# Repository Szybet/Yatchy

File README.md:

<h1 align="center">
  Yatchy
</h1>
<p align="center">
  <b>Y</b>our W<b>atchy</b>, fixed and improved, even made modular
</p>

Yatchy is a DIY watch, heavily inspired by the well known [watchy](https://watchy.sqfmi.com/). It focuses on fixing known issues and expanding the potential of it.

#### Key points:
- USBC instead of micro usb
- Better buttons, they won't break easily
- [Better battery life](https://github.com/Szybet/Yatchy/blob/main/hardware/power-consumption/README.md)
- Hardware hackable, easier to self assemble from scratch
- Fixed many issues and improved minor things
- A backlight is possible, *[kind of](https://github.com/Szybet/Yatchy/blob/main/3D/cases/README.md#proof-of-concept-glow-in-the-dark-transparent-filament-with-the-rotated-case)* and many other "extensions"
- [Smaller](https://github.com/Szybet/Yatchy/blob/main/faq.md#dimensions) form factor

<details>
  <summary><h3>Pictures</h3></summary>
The coolest yatchy, contributed by a community member!

<sub>My Yatchy, with a [titanium anodized case, the rotated variant](https://github.com/Szybet/Yatchy/blob/main/3D/cases/JLC3D.md#anodyzed-slm-titanium-tc4-no-polishing)</sub>

<sub>The battery is on the side because it's easier for me to measure power consumption, there are [cases with the battery inside](https://github.com/Szybet/Yatchy/tree/main/3D/cases)</sub>

<sub>A clean soldering job, with some alternative components (compability!)<sub>, yes, I know there is a short on the flex cable, it fell off when cleaning after the picture</sub></sub>

Watchy one the left yatchy on the right, yatchy is smaller (yes, the battery is outside, but it would only increase height, not width/length

<sub>Picture contributed, thanks!</sub>

</details>

## Yatchy features in more detail:

<h4>For regular users</h4>

- Heavy increase in battery life, even with the screen updating every minute <sub>(The esp32c6 has a riscv lp core, which i connected to the screen, which means the device never really wakes up fully to only update the screen, not only that i fixed sqfmi flaws (Using 2 voltage dividers for example) I also use the external crystal clock for the RTC which means no RTC IC... and many more such things)</sub>
- Better buttons, more solid, shouldn't and probably won't break that much if at all. They are also very quiet. If you like the tactile feel of the original buttons, you won't like these ones. Luckly vibration motor feedback is possible.
- Solid USB-C port <sub>(It's THT soldered)</sub>
- no more usb compability problems <sub>(Because the esp32c6 uses native jtag programming)</sub>
- better detection of charging, charge finishing. <sub>(In software it was hacky on the original watchy, there were problems with it, never worked good)</sub>
- support for more wireless protocols, home automation ones, wifi 6 too
- TVS diodes, voltage spike protection - which means no more destroyed devices because watchy doesn't follow any USB spec and allows your device to burn down...
- More precise time, based on some loose math and experiments, it should drift only a minute after a month, compared to the watchy its a lot better, **from experience it's even better than that**

<details>
  <summary><h4>For advanced users</h4></summary>

- Detailed ordering and assembly [guide](https://github.com/Szybet/Yatchy/tree/main/hardware/create-your-own)
- Detailed soldering and testing [guide](https://github.com/Szybet/Yatchy/blob/main/hardware/create-your-own/assembling.md)
- **A module area**, with almost all exposed pins from the esp, power lines, and many gpio pins thanks to the expander IC - You can create your own module, increase the capability of you yatchy without modifying everything inside - solar panel module, encoder instead of the button, sd card module, frontlight module, torchlight module, speaker module, microphone module, some environmental sensors. The only limitation is your imagination (And the size of the module)
   - The default module (In the picture above) allows for for attaching small things without the need for a custom PCB
- All the components are newer, still available and produced. They are also listed, with links to mauser / tme. Ordering a Yatchy PCB and the parts, soldering them themself is possible and easier than the watchy
- All QFN packages IC's on the board have increased pad sizes, so if you are skilled enough to solder QFN packages, here it will be easier
- I used traces teardrops, so more solid traces & pads
- A [hardware test program](https://github.com/Szybet/Yatchy/tree/main/hardware/create-your-own/test-program), which allows testing if all the pads of the esp32c6, which is the hardest part to solder are soldered correctly
- JTAG debugging via usb, yay

</details>

<details>
  <summary><h4>Flaws</h4></summary>

- No battery connector, the module pads are small - so it's not for everyone, harder to use / assembly (solder!) for beginners
- There is no dedicated place for the motor, it needs a dedicated place in the case. Soldering the motor cables also is not easy
- It's watchy like but not watchy case compatible, the size and form factor is the same but the obvious obstacle is USBC, even with it the buttons are different and placed a little off to save some space
- It's a 4 layer PCB, so a bit more costly (With JLCPCB it's still cheap)
- No easy hard reset option, you will need to short pins, but you probably won't need it. <sub>When developing the Yatchy, I only once needed a full reset</sub>
- A complicated license (but still open source!)

</details>

## Software
It's fully supported by [InkWatchy](https://github.com/Szybet/InkWatchy). Maybe a rust firmware in the future? We will see...

## Hardware sources, buying, reselling, license, battery life, time accuracy
Everything explained [here](https://github.com/Szybet/Yatchy/tree/main/hardware)

## Cases, 3D files of the pcb
[Cases here](https://github.com/Szybet/Yatchy/tree/main/3D/cases) and [pcb 3D model here](https://github.com/Szybet/Yatchy/tree/main/3D/pcb)

## [FAQ](https://github.com/Szybet/Yatchy/blob/main/faq.md)

# Community
Create a github issue or get in touch with me on the discord server or matrix space (on top of this read are links)

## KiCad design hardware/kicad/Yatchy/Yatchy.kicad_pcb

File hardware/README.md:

# Other related docs:
1. [Power consumption](https://github.com/Szybet/Yatchy/tree/main/hardware/power-consumption)
2. [Time accuracy](https://github.com/Szybet/Yatchy/blob/main/hardware/time-accuracy.md)
3. [Create your own](https://github.com/Szybet/Yatchy/tree/main/hardware/create-your-own)

## License
<sub>Read all of it :)</sub>

This work is licensed under a [Creative Commons (4.0 International License) Attribution—Noncommercial—Share Alike](https://creativecommons.org/licenses/by-nc-sa/4.0/)

Don't scream "IT'S NOT OPEN SOURCE", let me explain myself.

- First, this work is not a watchy fork, it's a complete redesign obviously inspired by the watchy form factor, but nothing more.
- I don't want SQFMI to steal this design and sell it. Not even if I could profit of it. His bad software, bad communication, sometimes bad and questionable hardware decisions have killed so much potential of the watchy.
- I don't want someone to just make money off it and give nothing back to the project. With that said, calm down, more on that in the commercial section below.
- I don't want for someone to rename it and take the credit for the hard work.

Is it too much to ask for? The whole issue above I have is very known in the open source world, you can see it everywhere around us, here is [Jeff](https://youtu.be/4aaF2HgTVe8?t=84) talking about it. If there appears a open source license which fixes this issue, I will switch to it. 

Oh did I mention **it's is open source anyway?\*\*\*** I share the full source, the schematic, the PCB source files, the needed* (more on it below) software. It's just not the pure open source definition, but the literal interpretation of it. Element of open source like contributing, forking etc. are still allowed and welcome, but with the restrictions above.

<details>
  <summary>Further thoughts about it:</summary>

On https://opensource.org/osd we can see, in the first point "Free Redistribution" and well, first "as a component" hardware can't be a component really, so this point doesn't apply to hardware. The whole point doesn't work for hardware, we know how the world works, it works for software, that's why [InkWatchy](https://github.com/Szybet/InkWatchy) is GPL3. Let's search further, on https://www.oshwa.org/faq/#what-license-to-use we can see the question "Won’t people rip me off?" exactly what I have been searching for! The answer is "Maybe"... ugh... Well their explanation is good but a maybe is too much for me... There is also that: https://mifactori.de/non-commercial-is-not-open-source/

The blog post just shows a general opinion / statement on the internet about this topic, some of the points there make sense to me but some not at all, like `Yes, you do. But so does every patent` Wtf even is this? Sharing something to file a patent is completly different from sharing everything to be reproductible. Also patents can't be compared to hardware things most often because patents say you created something new, but hardware is often a combination of other creations, not entirely new things. Open source is not just "It's commercial, you can ripp me off", it's more than that...

so the entire situation is a joke for me. I can't have a "open source" hardware license without someone "Maybe" ripping me off. So it looks like that:

What I want from "Open source":
- To allow people modify, build their own from scratch, even sell the hardware to some extend, do deep repairs etc. (Which I do, but I'm forced to use the `Creative Commons (4.0 International License) Attribution—Noncommercial—Share Alike` license.)

What I don't want:
- People ripping me off

Sad, it just looks like someone long time ago took a software license, applied it to hardware which doesn't work in the real world and started calling out everyone "Uh oh, it's actually not open source because you are not allowing people to ripp you off"

Rant end, here is what you are left with:

A device that is not open source from the strict definition, but has the bare source for replication available, with elements of open source allowed and the author is open about this all.

* * *

It's not only me having this opinion, other makers also share it:
- https://github.com/o7-machinehum/flipper-blackhat-a33#license

:)

</details>

Update 2026:

Prusa released the [Open community license](https://github.com/OpenCommunityLicence/OpenCommunityLicence) which is basically what I'm saying above but I allow a bit of commerciallity, so that's cool, if they release a plugin like the Micro Business one, but smaller (Nano business?) then I would switch fully to it, so it's less confussion.

## The design of the Yatchy
Yatchy was designed to:
- Be created by yourself. That means it's adjusted to be hand solderable. Sooo that means changed footprints for easier hand soldering. If you can solder SMD without a problem and QFN packets aren't scary for you, but BGA is a bit, then it's for you
- Extremely hackable and modular. The main point is the module and all exposed pads for it
- Optimisation of the ammount of different components, so cheaper
- I tried to use widely available IC's and components. For example, while using some highly mauser only specific IC could improve power consumption a small bit, I preffered the simplicity and availability of the current design

Those design choices have their own flaws:
- It's not possible to order a assembled yatchy from a manufacturer. Not only because of the module, but the modified footprints have not adjusted solder mask (And I don't have the experience and money to test it). **Also to be clear, a stencil is also untested, probably won't work for the reasons explained a sentence ago, you have been warned.** - And with that in mind, let's go to the commercial section

## Commercial
As mentioned above, It's not possible to manufacture yatchy on a mass scale (The original vision ones, doing a "regular" one, sure i gues). I don't even want to, I'm a student, I won't just start a company. I plan to sell a few Yatchy to community members and that's it.

But if you plan to create a Yatchy for yourself (because you have the skills required) you are fully allowed to do so! I will support it fully, you should also consider creating some for people who can't do that. I will fully support it too! Just remember to contribute some docs, code, help, small donation if you create some more and it will be fine :D

So "Commercial use" for the yatchy as in: using it as a cash grab, without giving anything back, which is not allowed.

If you plan to really mass produce them, then we should talk I ques.

**So you want to create your own? There is a doc for that: [Creating your own](https://github.com/Szybet/Yatchy/blob/main/hardware/create-your-own/README.md)**

## The ability to enforce the license
First some explanation:

Yatchy uses esp32c6 which has a lpcore which allows for updating time on the screen in a more efficient way, in a seperate program.

So all this talking is cool but it's just on paper, I can't enforce it, let's be real. That's why I will lock the full source code of the Yatchy lp program until I make back of what I invested. It costed more than I hoped for. Yatchy can still fully function without the lp core, just the battery life will be worse. I will share the source code partially to all yatchy users (also from other potential sellers) to allow to modify it, like the font used. Then I will simply compile it for them. **Yes, it could be converted into a binary library with a header api**, it was simply not done yet as the program is complicated and has a complicated structure. So that scenario is upon a possible request

More details [here](https://github.com/Szybet/Yatchy/blob/main/hardware/lpcore.md)

## The source files
Kicad version 9.0.3 is suggested.

In the kicad folder inside this directory are the design files for the yatchy v1, not yet tested

they (PCB's) are also a bit messy, not fully profesionall, but they do the job, I hope, as I will order them

Yes, the source files reference watchy in a few places, that's because the name "Yatchy" came after, at first this project was planned to be a small watchy fork.

Schematic, iBom can be seen here: https://szybet.github.io/Yatchy/hardware/read-only/index.html

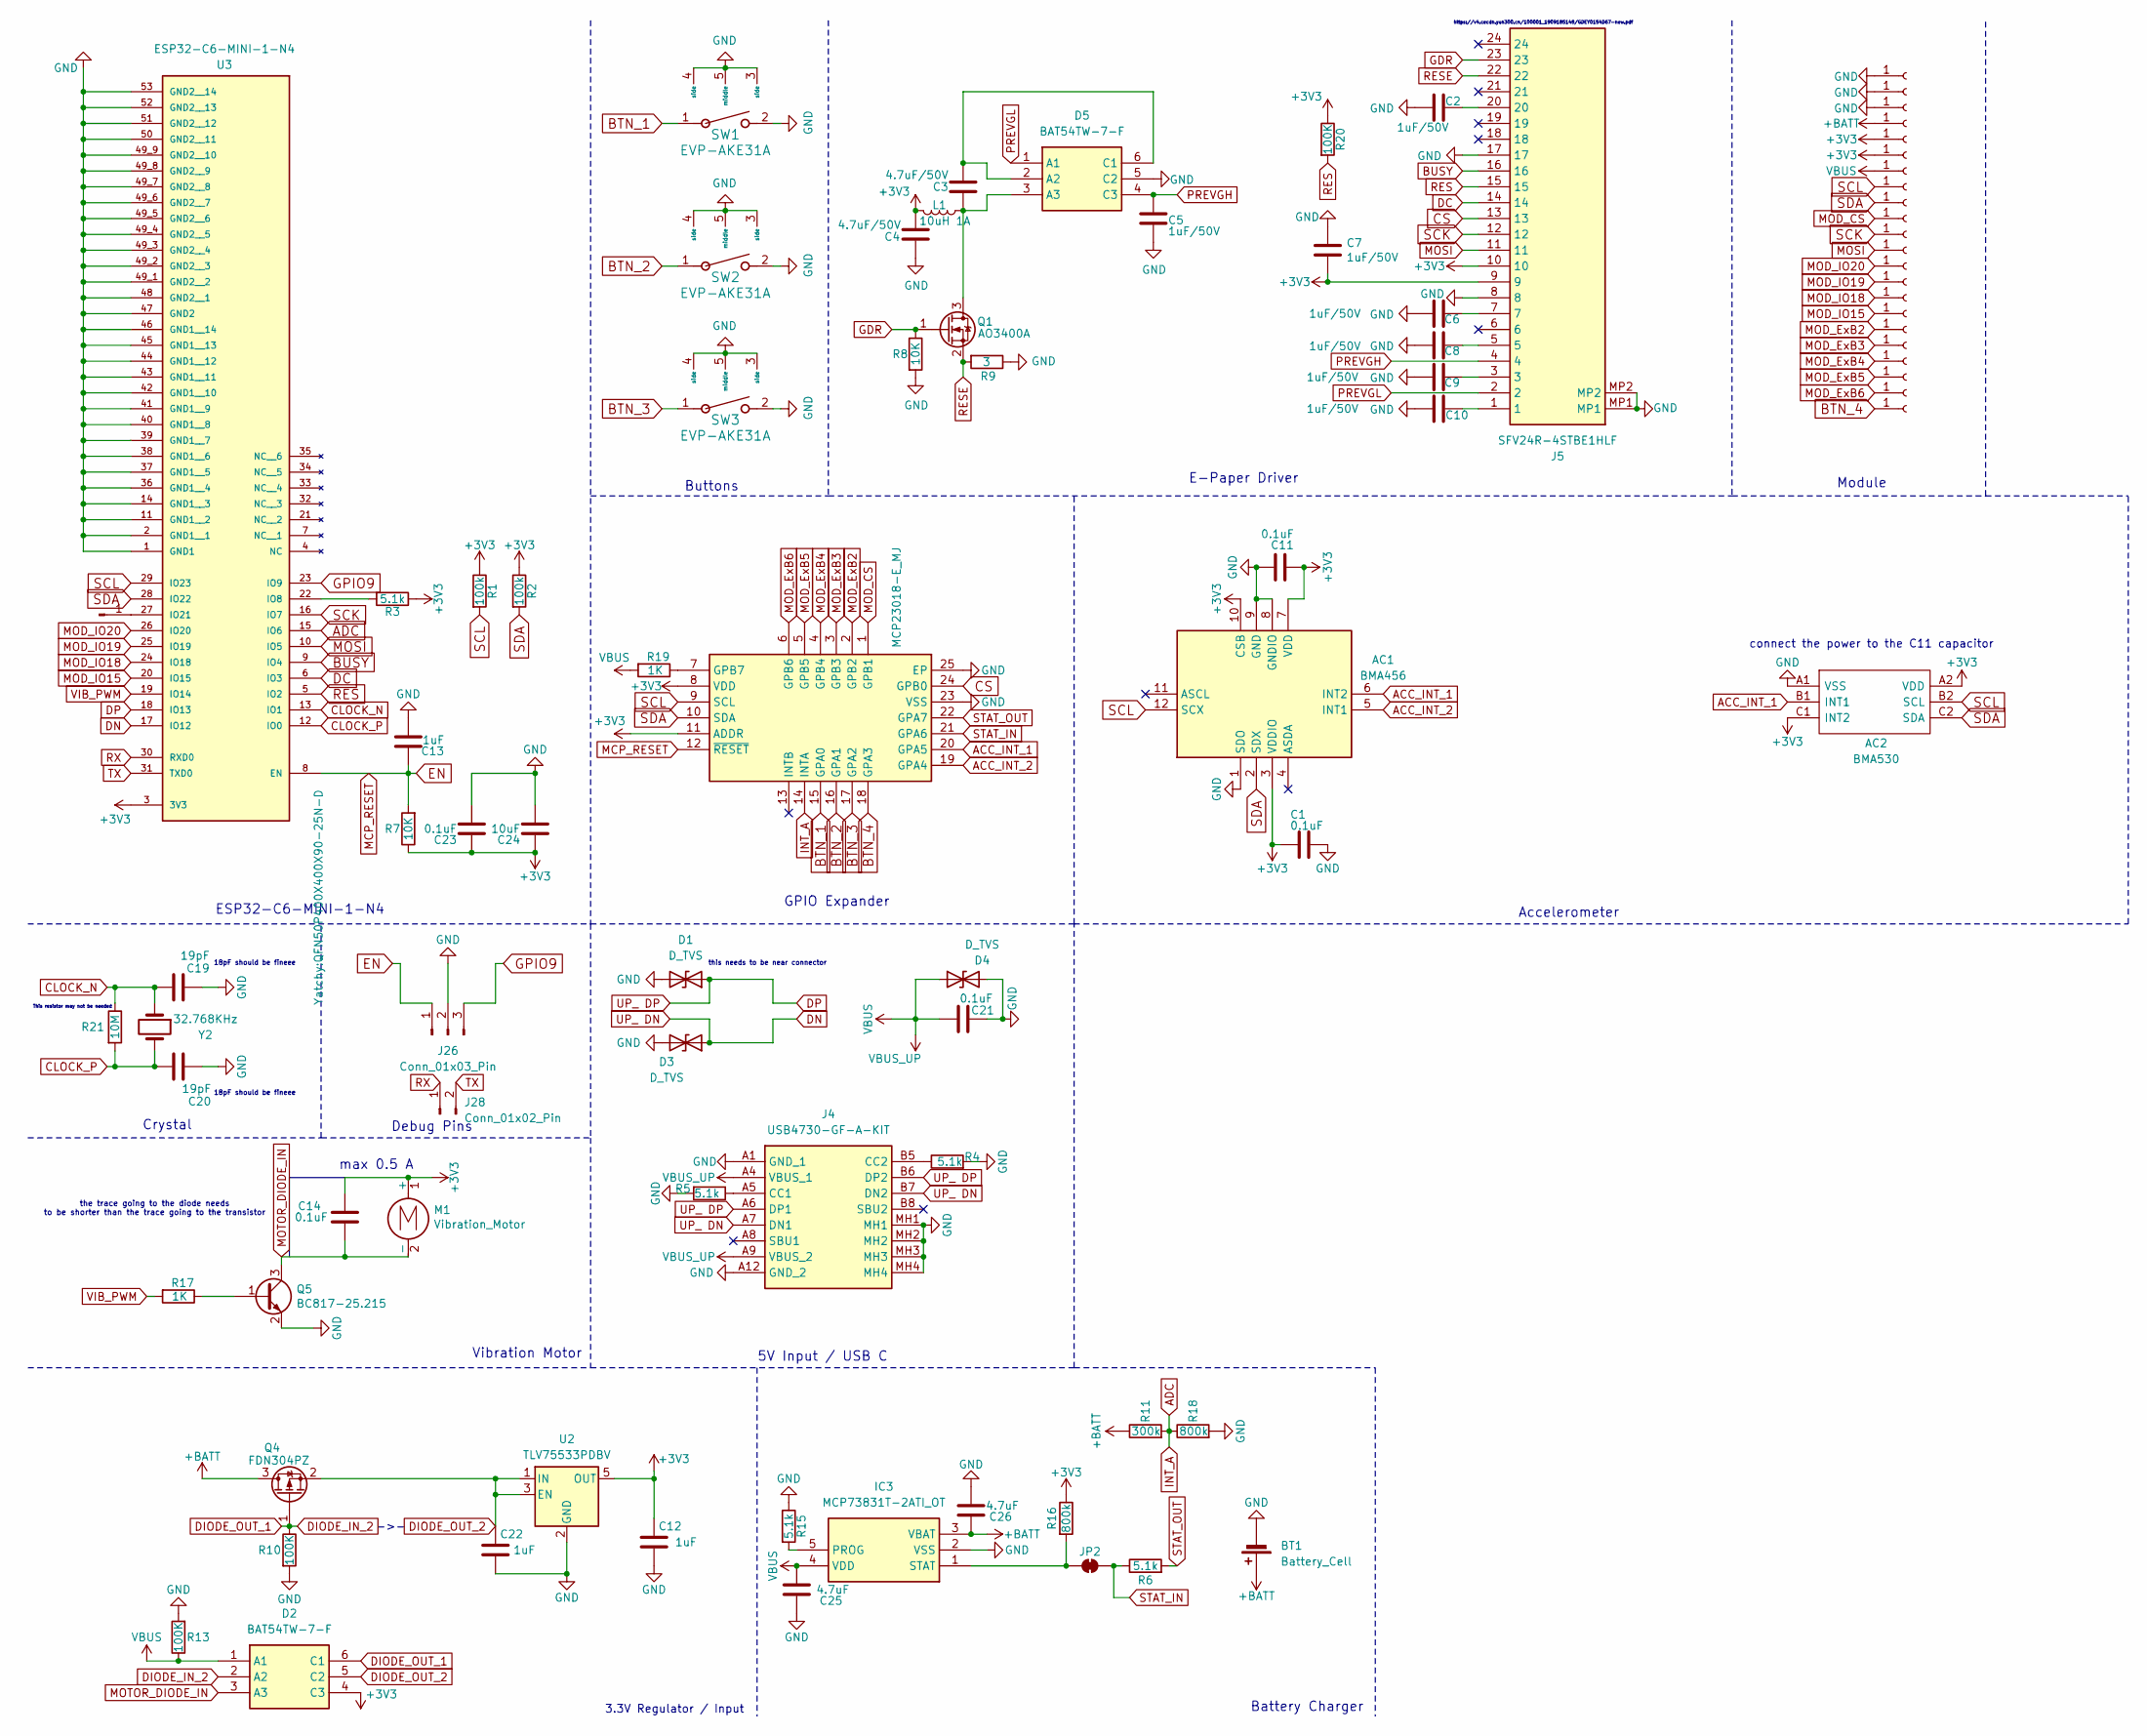
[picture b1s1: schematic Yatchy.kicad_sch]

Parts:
AC1: BMA456; BOSCH_LGA-12; Mouser Part Number 262-BMA456
AC2: BMA530; Mouser Part Number 262-BMA530
BT1: Battery_Cell; Battery_Header
C1, C11, C14, C21, C23: 0.1uF; C_0603_1608Metric
C2, C5, C6, C7, C8, C9, C10: 1uF/50V; C_0603_1608Metric
C3, C4: 4.7uF/50V; C_0805_2012Metric
C12, C13, C22: 1uF; C_0603_1608Metric
C19, C20: 19pF; C_0402_1005Metric
C24: 10uF; C_0603_1608Metric
C25, C26: 4.7uF; C_0805_2012Metric
D1, D3, D4: D_TVS; D_SOD-523
D2, D5: BAT54TW-7-F; SOT65P222X110-6N; Manufacturer_Part_Number BAT54TW-7-F
IC2: MCP23018-E_MJ; QFN50P400X400X90-25N-D; Manufacturer_Part_Number MCP23018-E/MJ
IC3: MCP73831T-2ATI_OT; SOT95P270X145-5N; Manufacturer_Part_Number MCP73831T-2ATI/OT
J1, J2, J3, J6, J7, J8, J9, J10, J11, J12, J13, J14, J15, J16, J19, J20, J21, J22, J23, J24, J25, J27: MOD_CONN; mod_Connector
J4: USB4730-GF-A-KIT; USB4730GFAKIT; Mouser Part Number 640-USB4730GFAKIT
J5: SFV24R-4STBE1HLF; SFV24R4STBE1HLF; Manufacturer_Part_Number SFV24R-4STBE1HLF
J17: Conn_01x01_Pin; testpoint
J26: Conn_01x03_Pin; PinHeader_1x03_P2.00mm_Horizontal_Small
J28: Conn_01x02_Pin; PinHeader_1x02_P2.00mm_Vertical
JP2: SolderJumper_2_Bridged; SolderJumper_Bridged_Small
L1: 10uH 1A; HPI0530-100
M1: Vibration_Motor; Motor_Header
Q1: AO3400A; SOT-23
Q4: FDN304PZ; SOT-23
Q5: BC817-25.215; SOT-23
R1, R2: 100k; R_0402_1005Metric
R3, R4, R5, R6, R15: 5.1k; R_0402_1005Metric
R7, R8: 10K; R_0402_1005Metric
R9: 3; R_0402_1005Metric
R10, R13, R20: 100K; R_0402_1005Metric
R11: 300k; R_0402_1005Metric
R16, R18: 800k; R_0402_1005Metric
R17, R19: 1K; R_0402_1005Metric
R21: 10M; R_0402_1005Metric
SW1, SW2, SW3: EVP-AKE31A; SW_EVP-AKE31A_PAN
U2: TLV75533PDBV; SOT-23-5
U3: ESP32-C6-MINI-1-N4; XCVR_ESP32-C6-MINI-1-N4; PARTREV 1.0
Y2: 32.768KHz; XTAL_9HT10_TXC

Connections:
+3V3: AC1.3 (VDDIO), AC1.7 (VDD), AC1.10 (CSB), AC2.A2 (VDD), AC2.C1 (INT2), C1.2, C4.1, C7.2, C11.2, C12.1, C14.1, C23.1, C24.1, D2.4 (C3), IC2.8 (VDD), IC2.11 (ADDR), J5.9, J5.10, J6.1, J25.1, L1.2, M1.1 (+), R1.1, R2.1, R3.1, R7.1, R16.1, R20.1, U2.5 (OUT), U3.3 (3V3)
+BATT: BT1.1 (+), C26.2, IC3.3 (VBAT), J3.1, Q4.3 (D), R11.1
ACC_INT_1: AC1.6 (INT2), AC2.B1 (INT1), IC2.20 (GPA5)
ACC_INT_2: AC1.5 (INT1), IC2.19 (GPA4)
ADC: IC2.14 (INTA), R11.2, R18.1, U3.15 (IO6)
BTN_1: IC2.15 (GPA0), SW1.1
BTN_2: IC2.16 (GPA1), SW2.1
BTN_3: IC2.17 (GPA2), SW3.1
BTN_4: IC2.18 (GPA3), J24.1
BUSY: J5.16, U3.9 (IO4)
CLOCK_N: C19.1, R21.1, U3.13 (IO1), Y2.1
CLOCK_P: C20.1, R21.2, U3.12 (IO0), Y2.2
CS: IC2.24 (GPB0), J5.13
DC: J5.14, U3.6 (IO3)
DIODE_IN_2: D2.2 (A2), D2.6 (C1), Q4.1 (G), R10.1
DIODE_OUT_2: C22.1, D2.5 (C2), Q4.2 (S), U2.1 (IN), U2.3 (EN)
DN: D3.1 (A1), J4.A7 (DN1), J4.B7 (DN2), U3.17 (IO12)
DP: D1.1 (A1), J4.A6 (DP1), J4.B6 (DP2), U3.18 (IO13)
EN: C13.1, IC2.12 (~RESET), J26.1, R7.2, U3.8 (EN)
GDR: J5.23, Q1.1 (G), R8.1
GND: AC1.1 (SDO), AC1.8 (GNDIO), AC1.9 (GND), AC2.A1 (VSS), BT1.2 (-), C1.1, C2.2, C4.2, C5.2, C6.2, C7.1, C8.2, C9.2, C10.2, C11.1, C12.2, C13.2, C19.2, C20.2, C21.2, C22.2, C23.2, C24.2, C25.2, C26.1, D1.2 (A2), D3.2 (A2), D4.2 (A2), D5.5 (C2), IC2.23 (VSS), IC2.25 (EP), IC3.2 (VSS), J1.1, J2.1, J4.A1 (GND_1), J4.A12 (GND_2), J4.MH1, J4.MH2, J4.MH3, J4.MH4, J5.8, J5.17, J5.MP1, J5.MP2, J26.2, J27.1, Q5.2 (E), R4.2, R5.2, R8.2, R9.1, R10.2, R13.2, R15.1, R18.2, SW1.2, SW1.3 (side), SW1.4 (side), SW1.5 (middle), SW2.2, SW2.3 (side), SW2.4 (side), SW2.5 (middle), SW3.2, SW3.3 (side), SW3.4 (side), SW3.5 (middle), U2.2 (GND), U3.1 (GND1), U3.2 (GND1__1), U3.11 (GND1__2), U3.14 (GND1__3), U3.36 (GND1__4), U3.37 (GND1__5), U3.38 (GND1__6), U3.39 (GND1__7), U3.40 (GND1__8), U3.41 (GND1__9), U3.42 (GND1__10), U3.43 (GND1__11), U3.44 (GND1__12), U3.45 (GND1__13), U3.46 (GND1__14), U3.47 (GND2), U3.48 (GND2__1), U3.49_1 (GND2__2), U3.49_2 (GND2__3), U3.49_3 (GND2__4), U3.49_4 (GND2__5), U3.49_5 (GND2__6), U3.49_6 (GND2__7), U3.49_7 (GND2__8), U3.49_8 (GND2__9), U3.49_9 (GND2__10), U3.50 (GND2__11), U3.51 (GND2__12), U3.52 (GND2__13), U3.53 (GND2__14)
GPIO9: J26.3, U3.23 (IO9)
MOD_CS: IC2.1 (GPB1), J10.1
MOD_ExB2: IC2.2 (GPB2), J19.1
MOD_ExB3: IC2.3 (GPB3), J20.1
MOD_ExB4: IC2.4 (GPB4), J21.1
MOD_ExB5: IC2.5 (GPB5), J22.1
MOD_ExB6: IC2.6 (GPB6), J23.1
MOD_IO15: J16.1, U3.20 (IO15)
MOD_IO18: J15.1, U3.24 (IO18)
MOD_IO19: J14.1, U3.25 (IO19)
MOD_IO20: J13.1, U3.26 (IO20)
MOSI: J5.11, J12.1, U3.10 (IO5)
MOTOR_DIODE_IN: C14.2, D2.3 (A3), M1.2 (-), Q5.3 (C)
unnamed: C2.1, J5.20
unnamed: C6.1, J5.7
unnamed: C8.1, J5.5
unnamed: C9.1, J5.3
unnamed: C10.1, J5.1
unnamed: C3.1, D5.2 (A2), D5.6 (C1)
unnamed: C3.2, D5.3 (A3), L1.1, Q1.3 (D)
unnamed: IC2.7 (GPB7), R19.1
unnamed: IC3.5 (PROG), R15.2
unnamed: IC3.1 (STAT), JP2.1 (A), R16.2
unnamed: J4.A5 (CC1), R5.1
unnamed: J4.B5 (CC2), R4.1
unnamed: J17.1, U3.27 (IO21)
unnamed: Q5.1 (B), R17.1
unnamed: R3.2, U3.22 (IO8)
PREVGH: C5.1, D5.4 (C3), J5.4
PREVGL: D5.1 (A1), J5.2
RES: J5.15, R20.2, U3.5 (IO2)
RESE: J5.22, Q1.2 (S), R9.2
RX: J28.1, U3.30 (RXD0)
SCK: J5.12, J11.1, U3.16 (IO7)
SCL: AC1.12 (SCX), AC2.B2 (SCL), IC2.9 (SCL), J8.1, R1.2, U3.29 (IO23)
SDA: AC1.2 (SDX), AC2.C2 (SDA), IC2.10 (SDA), J9.1, R2.2, U3.28 (IO22)
STAT_IN: IC2.21 (GPA6), JP2.2 (B), R6.1
STAT_OUT: IC2.22 (GPA7), R6.2
TX: J28.2, U3.31 (TXD0)
VBUS: C21.1, C25.1, D2.1 (A1), D4.1 (A1), IC3.4 (VDD), J4.A4 (VBUS_1), J4.A9 (VBUS_2), J7.1, R13.1, R19.2
VIB_PWM: R17.2, U3.19 (IO14)

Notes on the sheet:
This resistor may not be needed
->-
ESP32-C6-MINI-1-N4
the trace going to the diode needs to be shorter than the trace going to the transistor
18pF should be fineee
5V Input / USB C
Battery Charger
Buttons
connect the power to the C11 capacitor
Vibration Motor
max 0.5 A
GPIO Expander
Crystal
Module
3.3V Regulator / Input
https://v4.cecdn.yun300.cn/100001_1909185148/GDEY0154D67-new.pdf
Debug Pins
this needs to be near connector
Accelerometer
E-Paper Driver

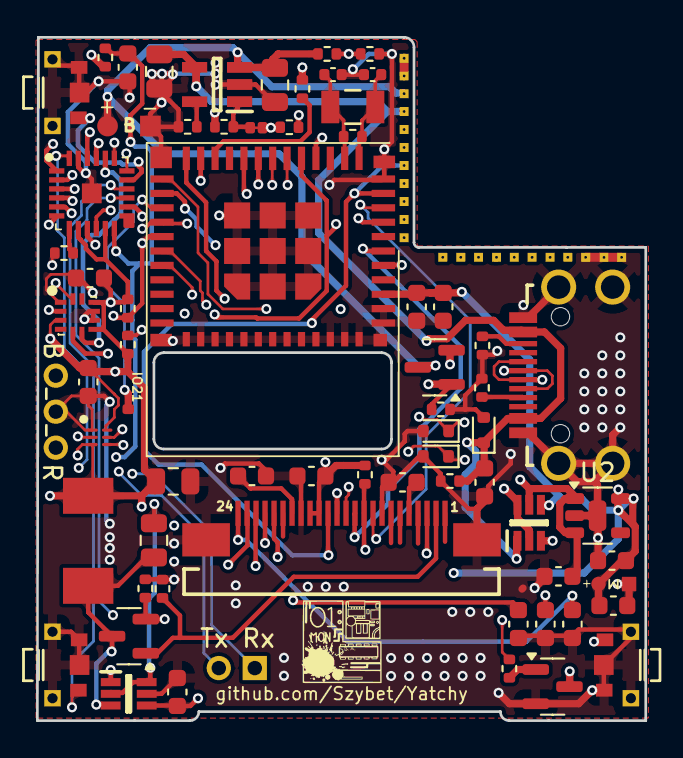
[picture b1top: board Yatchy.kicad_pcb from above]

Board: 4 copper layers, 33.8 x 38.0 mm, 90 parts (0 on the bottom side), 62 nets.

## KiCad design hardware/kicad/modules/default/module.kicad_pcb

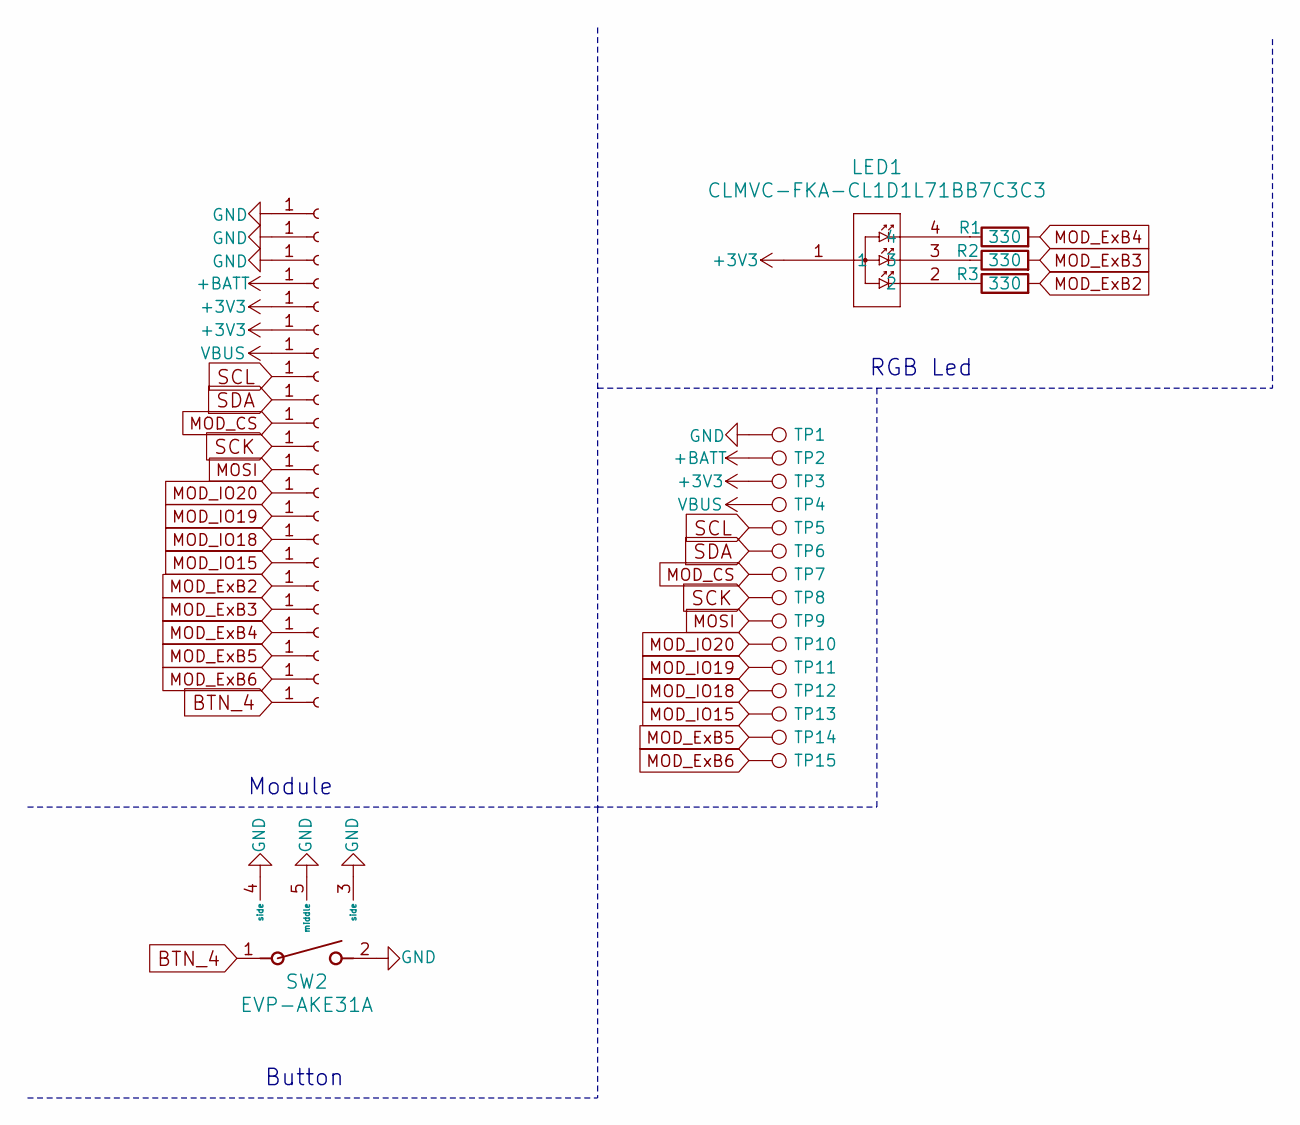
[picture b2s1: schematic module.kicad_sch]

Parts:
J1, J2, J3, J4, J5, J6, J7, J8, J9, J10, J11, J12, J13, J14, J15, J16, J17, J18, J19, J20, J21, J22: MOD_CONN; mod_Connector
LED1: CLMVC-FKA-CL1D1L71BB7C3C3; CLMVC-FKA-CL1D1L71BB7C3C3_CRE
R1, R2, R3: 330; R_0402_1005Metric
SW2: EVP-AKE31A; SW_EVP-AKE31A_PAN
TP1, TP2, TP3, TP4, TP5, TP6, TP7, TP8, TP9, TP10, TP11, TP12, TP13, TP14, TP15: TestPoint; TestPoint_THTPad_D1.0mm_Drill0.5mm

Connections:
+3V3: J5.1, J6.1, LED1.1, TP3.1; also elsewhere on the board
+BATT: J4.1, TP2.1
BTN_4: J22.1, SW2.1
GND: J1.1, J2.1, J3.1, SW2.2, SW2.3 (side), SW2.4 (side), SW2.5 (middle), TP1.1
MOD_CS: J10.1, TP7.1
MOD_ExB2: J17.1, R3.2; also elsewhere on the board
MOD_ExB3: J18.1, R2.2; also elsewhere on the board
MOD_ExB4: J19.1, R1.2; also elsewhere on the board
MOD_ExB5: J20.1, TP14.1; also elsewhere on the board
MOD_ExB6: J21.1, TP15.1
MOD_IO15: J16.1, TP13.1
MOD_IO18: J15.1, TP12.1
MOD_IO19: J14.1, TP11.1
MOD_IO20: J13.1, TP10.1
MOSI: J12.1, TP9.1
unnamed 16: LED1.2, R3.1; also elsewhere on the board
unnamed 17: LED1.3, R2.1; also elsewhere on the board
unnamed 18: LED1.4, R1.1; also elsewhere on the board
SCK: J11.1, TP8.1
SCL: J8.1, TP5.1
SDA: J9.1, TP6.1
VBUS: J7.1, TP4.1

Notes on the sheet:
RGB Led
Button
Module

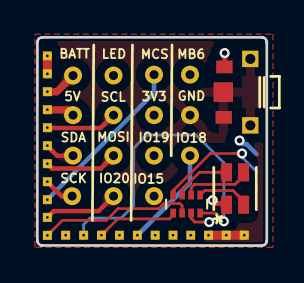
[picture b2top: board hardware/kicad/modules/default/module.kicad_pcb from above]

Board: 4 copper layers, 12.7 x 11.6 mm, 41 parts (1 on the bottom side), 23 nets.

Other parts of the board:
D1: LED; LED_0402_1005Metric
RN1: 330 ohm; R_Array_Concave_4x0402

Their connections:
+3V3: D1.2 (A); also elsewhere on the board
MOD_ExB2: RN1.2 (R2.1); also elsewhere on the board
MOD_ExB3: RN1.3 (R3.1); also elsewhere on the board
MOD_ExB4: RN1.4 (R4.1); also elsewhere on the board
MOD_ExB5: RN1.1 (R1.1); also elsewhere on the board
unnamed: D1.1 (K), RN1.8 (R1.2)
unnamed 16: RN1.7 (R2.2); also elsewhere on the board
unnamed 17: RN1.6 (R3.2); also elsewhere on the board
unnamed 18: RN1.5 (R4.2); also elsewhere on the board

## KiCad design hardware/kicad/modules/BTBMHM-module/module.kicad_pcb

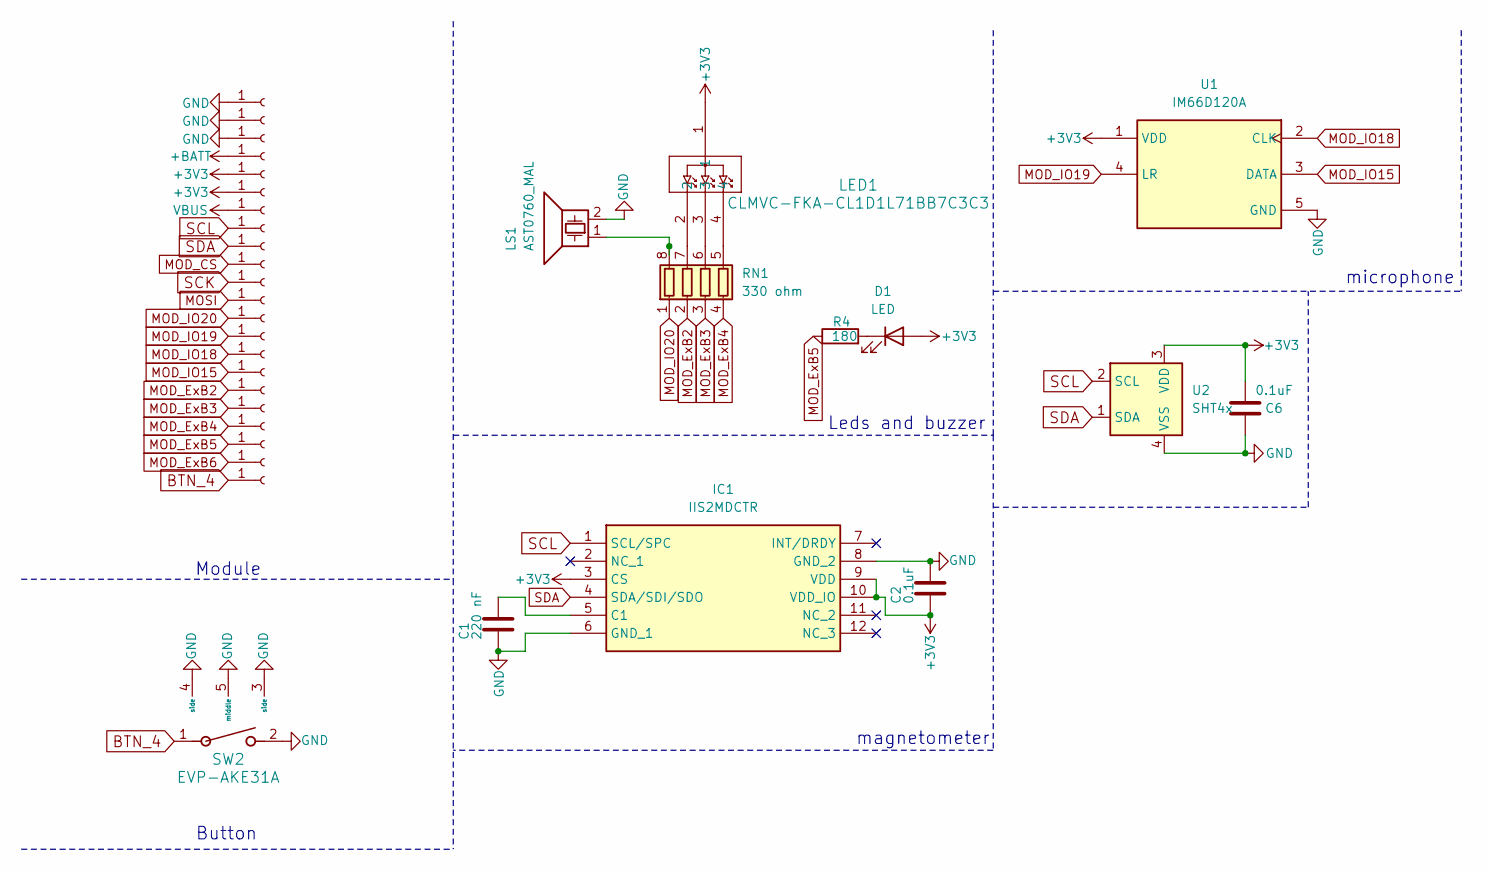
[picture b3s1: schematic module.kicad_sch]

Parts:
C1: 220 nF; C_0603_1608Metric
C2, C6: 0.1uF; C_0603_1608Metric
D1: LED; LED_0402_1005Metric
IC1: IIS2MDCTR; BOSCH_LGA-12; Mouser Part Number 511-IIS2MDCTR
J1, J2, J3, J4, J5, J6, J7, J8, J9, J10, J11, J12, J13, J14, J15, J16, J17, J18, J19, J20, J21, J22: MOD_CONN; mod_Connector
LED1: CLMVC-FKA-CL1D1L71BB7C3C3; CLMVC-FKA-CL1D1L71BB7C3C3_CRE
LS1: AST0760_MAL
R4: 180; R_0402_1005Metric
RN1: 330 ohm; R_Array_Concave_4x0402
SW2: EVP-AKE31A; SW_EVP-AKE31A_PAN
U1: IM66D120A; IFX-PG-TLGA-5-6-V
U2: SHT4x; Sensirion_DFN-4_1.5x1.5mm_P0.8mm_SHT4x_NoCentralPad

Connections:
+3V3: C2.2, C6.2, D1.2 (A), IC1.3 (CS), IC1.9 (VDD), IC1.10 (VDD_IO), J5.1, J6.1, LED1.1, U1.1 (VDD), U2.3 (VDD)
+BATT: J4.1
BTN_4: J22.1, SW2.1
GND: C1.2, C2.1, C6.1, IC1.6 (GND_1), IC1.8 (GND_2), J1.1, J2.1, J3.1, LS1.2, SW2.2, SW2.3 (side), SW2.4 (side), SW2.5 (middle), U1.5 (GND), U2.4 (VSS)
MOD_CS: J10.1
MOD_ExB2: J17.1, RN1.2 (R2.1)
MOD_ExB3: J18.1, RN1.3 (R3.1)
MOD_ExB4: J19.1, RN1.4 (R4.1)
MOD_ExB5: J20.1, R4.1
MOD_ExB6: J21.1
MOD_IO15: J16.1, U1.3 (DATA)
MOD_IO18: J15.1, U1.2 (CLK)
MOD_IO19: J14.1, U1.4 (LR)
MOD_IO20: J13.1, RN1.1 (R1.1)
MOSI: J12.1
unnamed: D1.1 (K), R4.2
unnamed: C1.1, IC1.5 (C1)
unnamed: LS1.1, RN1.8 (R1.2)
unnamed: LED1.2, RN1.7 (R2.2)
unnamed: LED1.3, RN1.6 (R3.2)
unnamed: LED1.4, RN1.5 (R4.2)
SCK: J11.1
SCL: IC1.1 (SCL/SPC), J8.1, U2.2 (SCL)
SDA: IC1.4 (SDA/SDI/SDO), J9.1, U2.1 (SDA)
VBUS: J7.1

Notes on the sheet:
magnetometer
microphone
Button
Leds and buzzer
Module

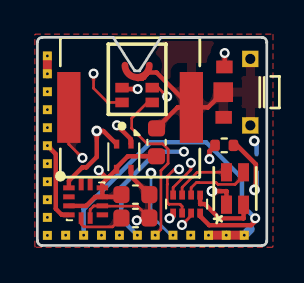
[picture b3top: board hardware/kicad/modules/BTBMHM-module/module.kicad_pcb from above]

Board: 4 copper layers, 12.7 x 11.6 mm, 34 parts (1 on the bottom side), 19 nets.

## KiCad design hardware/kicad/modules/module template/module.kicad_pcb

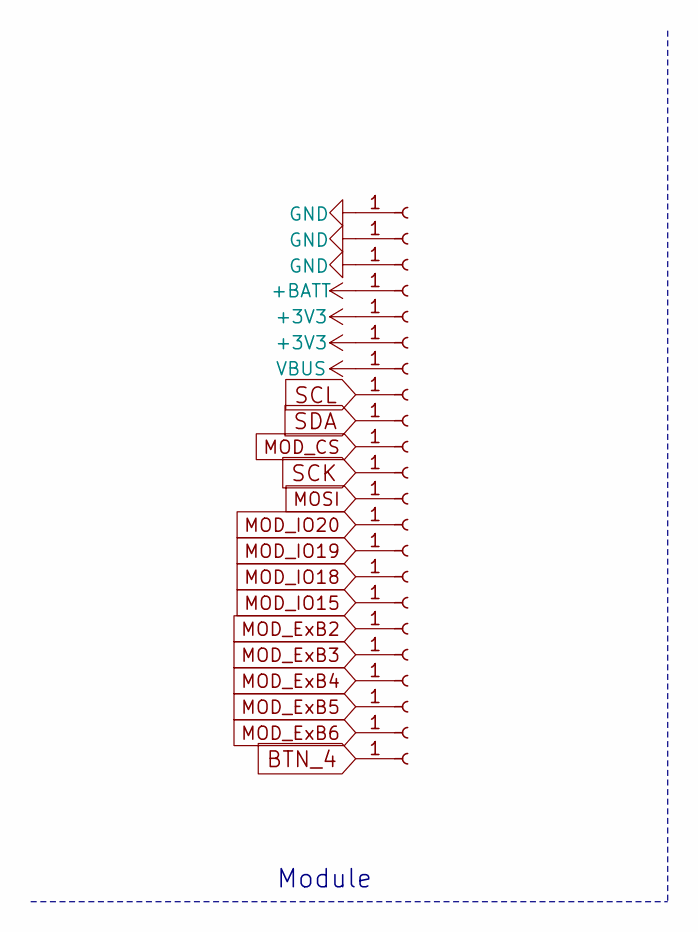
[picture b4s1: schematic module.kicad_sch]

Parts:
J1, J2, J3, J4, J5, J6, J7, J8, J9, J10, J11, J12, J13, J14, J15, J16, J17, J18, J19, J20, J21, J22: MOD_CONN; mod_Connector

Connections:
+3V3: J5.1, J6.1
+BATT: J4.1
BTN_4: J22.1
GND: J1.1, J2.1, J3.1
MOD_CS: J10.1
MOD_ExB2: J17.1
MOD_ExB3: J18.1
MOD_ExB4: J19.1
MOD_ExB5: J20.1
MOD_ExB6: J21.1
MOD_IO15: J16.1
MOD_IO18: J15.1
MOD_IO19: J14.1
MOD_IO20: J13.1
MOSI: J12.1
SCK: J11.1
SCL: J8.1
SDA: J9.1
VBUS: J7.1

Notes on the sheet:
Module

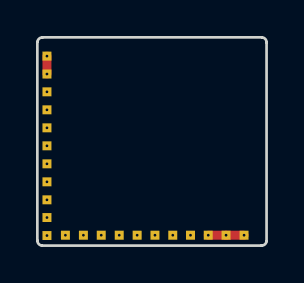
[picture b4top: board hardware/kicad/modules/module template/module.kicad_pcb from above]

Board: 4 copper layers, 12.7 x 11.6 mm, 22 parts (0 on the bottom side), 2 nets.

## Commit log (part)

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2024-06-27 push img
2024-06-27 small img
2024-08-01 test program
2024-08-04 any pin flex pin madness, not yet working
2024-08-05 working gpio test
2024-11-07 create
2024-11-07 add hardware
2024-11-07 add pdf
2024-11-28 fix test program
2024-11-28 serial too
2024-11-29 add usb pins when using serial
2024-11-29 ignore pin 13 and disable jtag when uart
2024-12-01 change motor transistor name
2024-12-20 add wv2c
2024-12-25 fix module 3d models
2025-01-31 change tvs diode fix module and calc
2025-01-31 move components
2025-02-01 remove mouse bites
2025-02-01 fix outline
2025-04-15 brick case
2025-04-25 reminders of risk
2025-04-26 fix test program I fogor wat
2025-04-26 test program improvements
2025-05-12 fix components-calc based on bom file, add 1K resistor to gpio expander 5V connection, change 50K resistor to 100K
2025-07-04 case patches
2025-07-10 Create rotated
2025-07-10 Create rotated img
2025-07-10 add images
2025-07-10 optimize images
2025-07-10 render
2025-07-22 rename file
2025-07-22 connect mcp reset pin with esp32c6
2025-08-03 add 1A ldo
2025-08-22 test program esp flash check
2025-08-23 move test program to usb
2025-08-23 Some quality of life improvements to the pcb, applied suggestions to the pcb
2025-08-23 zone refill forgot
2025-08-25 clean
2025-08-25 improve module silkscreen
2025-08-27 Add screen, expose test point
2025-08-27 fix dfm and screen footprint
2025-08-28 Add silkscreen
2025-08-31 add thermal pad voltage regulator
2025-09-12 Automatic generation of schematics and iboms
2025-09-12 index html
2025-09-12 dark mode
2025-09-12 only F
2025-09-12 some more default options
2025-09-14 add new module
2025-09-14 rename & improve site
2025-09-16 add case
2025-09-16 compress
2025-09-16 add to table
2025-09-16 better image
2025-09-16 another pic
2025-09-25 move things around
2025-09-25 repair dead links
2025-09-25 move things
2025-09-25 cleanout
2025-10-15 Rename image.png to slicerslicedlinefiles.png
2025-10-18 Rename IMG_20251016_062135.jpg to sidepurplecase.jpg
2025-10-18 Rename image.png to Paintonsupportblockers.png
2025-10-18 Rename IMG_20251016_062204.jpg to Orangeonepiecestrap.jpg
2025-10-18 Rename IMG_20251016_062156.jpg to Rearofpurplecase.jpg
2025-10-18 Rename IMG_20251016_062152.jpg to Frontpurplecase.jpg
2025-10-19 modimage
2025-10-20 imagechang
2025-10-20 readmedit
2026-02-16 Fix link
2026-03-13 Update to newer libs
2026-03-13 c6 builds, not sure
2026-03-13 everything builds
2026-03-20 uart
2026-03-20 fixes
2026-04-24 michal case
